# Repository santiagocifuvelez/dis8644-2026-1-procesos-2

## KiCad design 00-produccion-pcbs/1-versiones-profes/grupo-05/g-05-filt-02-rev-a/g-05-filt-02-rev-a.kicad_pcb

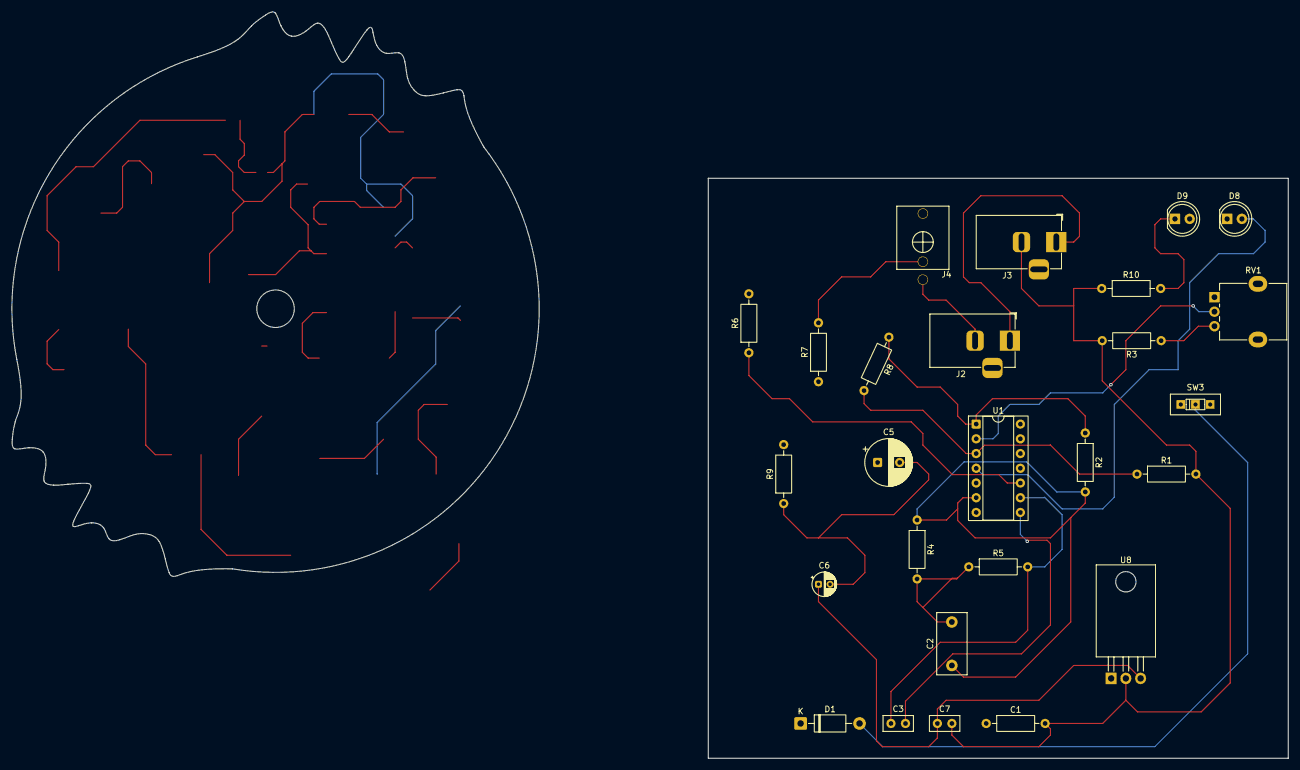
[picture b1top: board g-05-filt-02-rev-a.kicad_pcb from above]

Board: 2 copper layers, 100.0 x 100.0 mm, 26 parts (0 on the bottom side), 16 nets.

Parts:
C1: 1uf; R_Axial_DIN0207_L6.3mm_D2.5mm_P10.16mm_Horizontal
C2: 33n; C_Disc_D10.5mm_W5.0mm_P7.50mm
C3: 10n; C_Disc_D5.0mm_W2.5mm_P2.50mm
C5: 100u; CP_Radial_D8.0mm_P3.80mm
C6: 10u; CP_Radial_D4.0mm_P2.00mm
C7: 100n; C_Disc_D5.0mm_W2.5mm_P2.50mm
D1: 1N4007; D_DO-41_SOD81_P10.16mm_Horizontal
D8, D9: LED; LED_D5.0mm
J2, J3: Barrel_Jack_Switch; BarrelJack_Horizontal
J4: AudioJack2_SwitchT; PJ301M-12
R1: 22k; R_Axial_DIN0207_L6.3mm_D2.5mm_P10.16mm_Horizontal
R2, R3: 10k; R_Axial_DIN0207_L6.3mm_D2.5mm_P10.16mm_Horizontal
R4, R5, R6, R8: 100k; R_Axial_DIN0207_L6.3mm_D2.5mm_P10.16mm_Horizontal
R7: 220k; R_Axial_DIN0207_L6.3mm_D2.5mm_P10.16mm_Horizontal
R9, R10: 1k; R_Axial_DIN0207_L6.3mm_D2.5mm_P10.16mm_Horizontal
RV1: 100k; Potentiometer_Alpha_RD901F-40-00D_Single_Vertical
SW3: SW_SPDT; spdt_ssd12d00g3
U1: LM324; DIP-14_W7.62mm_Socket
U8: L7805; TO-220-3_Horizontal_TabDown

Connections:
+5V: C6.1, C7.1, D8.2 (A), U1.4 (V+), U8.3 (OUT)
+12V: C5.1, D1.1 (K), U8.1 (IN)
GND: C1.2, C5.2, C6.2, C7.2, J2.2, J3.2, J4.1, R1.2, R3.2, R6.2, R9.1, R10.1, U1.11 (V-), U8.2 (GND)
unnamed: C2.2, R4.2, R5.1, U1.7
unnamed: D1.2 (A), SW3.2 (B)
unnamed: D8.1 (K), R9.2
unnamed: C3.2, D9.2 (A), J4.3, R7.2, U1.8
unnamed: D9.1 (K), R10.2
unnamed: R2.1, R8.1, U1.1
unnamed: J2.1, J3.1, SW3.1 (A)
unnamed: R1.1, R8.2, U1.3 (+)
unnamed: C1.1, RV1.2, U1.2 (-)
unnamed: C2.1, R2.2, R4.1, U1.6 (+)
unnamed: R3.1, RV1.3, U1.5 (-)
unnamed: C3.1, R5.2, R7.1, U1.9 (+)
unnamed: R6.1, U1.10 (-)

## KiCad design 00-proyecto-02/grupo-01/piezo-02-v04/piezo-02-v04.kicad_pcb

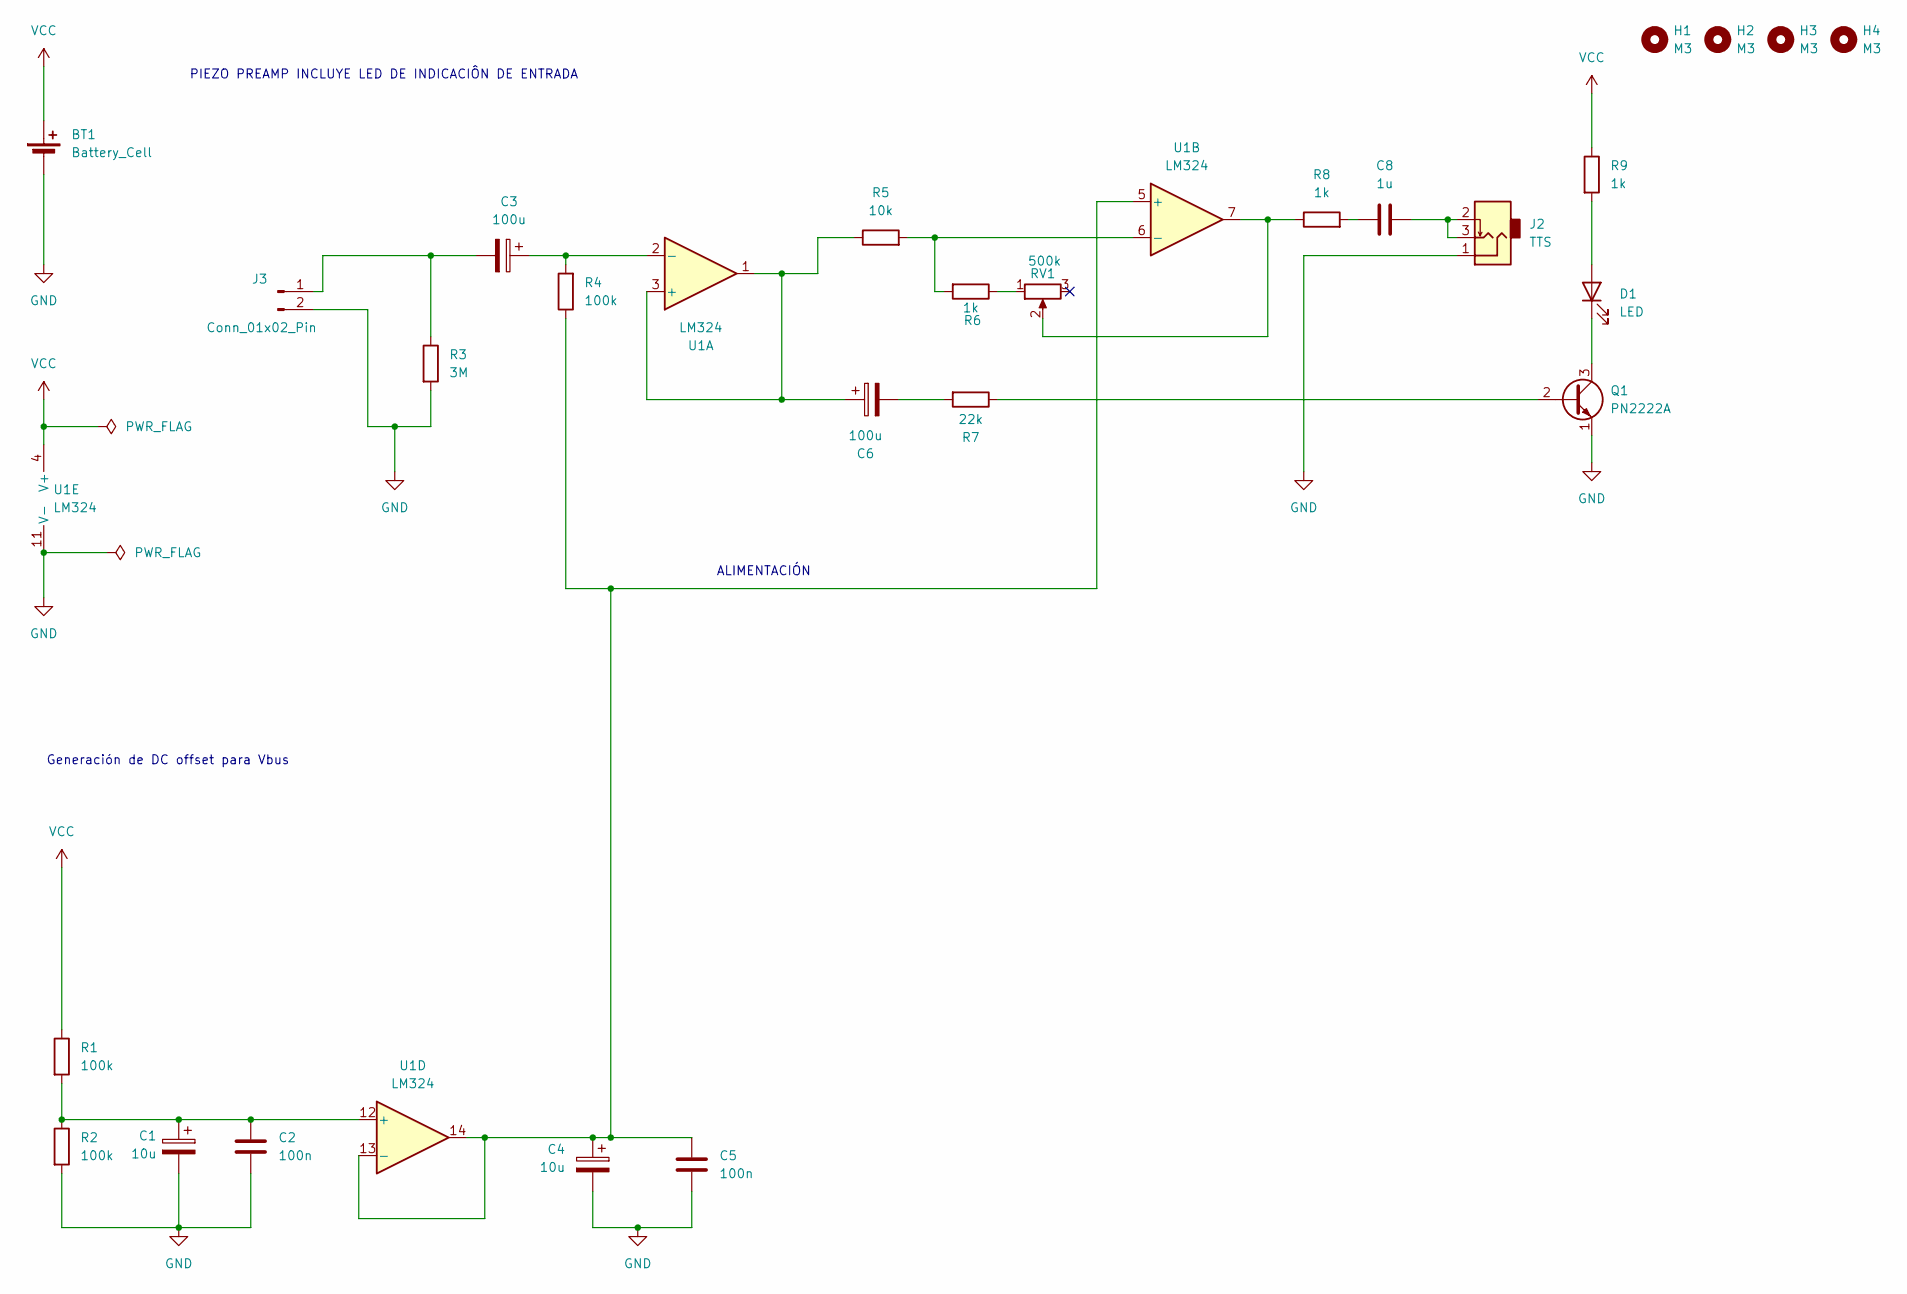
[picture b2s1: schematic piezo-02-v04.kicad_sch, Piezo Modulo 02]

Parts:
BT1: Battery_Cell; TerminalBlock_MaiXu_MX126-5.0-02P_1x02_P5.00mm
C1, C4: 10u; CP_Radial_D4.0mm_P2.00mm
C2, C5: 100n; C_Disc_D5.0mm_W2.5mm_P2.50mm
C3, C6: 100u; CP_Radial_D8.0mm_P3.80mm
C8: 1u; C_Disc_D5.0mm_W2.5mm_P5.00mm
D1: LED; LED_D5.0mm
H1, H2, H3, H4: M3; MountingHole_3.2mm_M3
J2: TTS; PJ301M-12
J3: Conn_01x02_Pin; PinSocket_1x02_P2.54mm_Vertical
Q1: PN2222A; TO-92_Inline
R1, R2, R4: 100k; R_Axial_DIN0207_L6.3mm_D2.5mm_P10.16mm_Horizontal
R3: 3M; R_Axial_DIN0207_L6.3mm_D2.5mm_P10.16mm_Horizontal
R5: 10k; R_Axial_DIN0207_L6.3mm_D2.5mm_P10.16mm_Horizontal
R6, R8, R9: 1k; R_Axial_DIN0207_L6.3mm_D2.5mm_P10.16mm_Horizontal
R7: 22k; R_Axial_DIN0207_L6.3mm_D2.5mm_P10.16mm_Horizontal
RV1: 500k; Potentiometer_Alps_RK163_Single_Horizontal
U1: LM324; DIP-14_W7.62mm_LongPads

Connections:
GND: BT1.2 (-), C1.2, C2.2, C4.2, C5.2, J2.1, J3.2, Q1.1 (E), R2.2, R3.2, U1.11 (V-)
unnamed: C6.2, R7.2
unnamed: C8.1, R8.2
unnamed: C8.2, J2.2, J2.3
unnamed: D1.2 (A), R9.2
unnamed: D1.1 (K), Q1.3 (C)
unnamed: C3.2, J3.1, R3.1
unnamed: Q1.2 (B), R7.1
unnamed: R6.1, RV1.1
unnamed: R8.1, RV1.2, U1.7
unnamed: C6.1, R5.1, U1.1, U1.3 (+)
unnamed: C3.1, R4.2, U1.2 (-)
unnamed: C4.1, C5.1, R4.1, U1.5 (+), U1.13 (-), U1.14
unnamed: R5.2, R6.2, U1.6 (-)
unnamed: C1.1, C2.1, R1.2, R2.1, U1.12 (+)
VCC: BT1.1 (+), R1.1, R9.1, U1.4 (V+)

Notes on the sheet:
PIEZO PREAMP INCLUYE LED DE INDICACIÔN DE ENTRADA
ALIMENTACIÓN
Generación de DC offset para Vbus

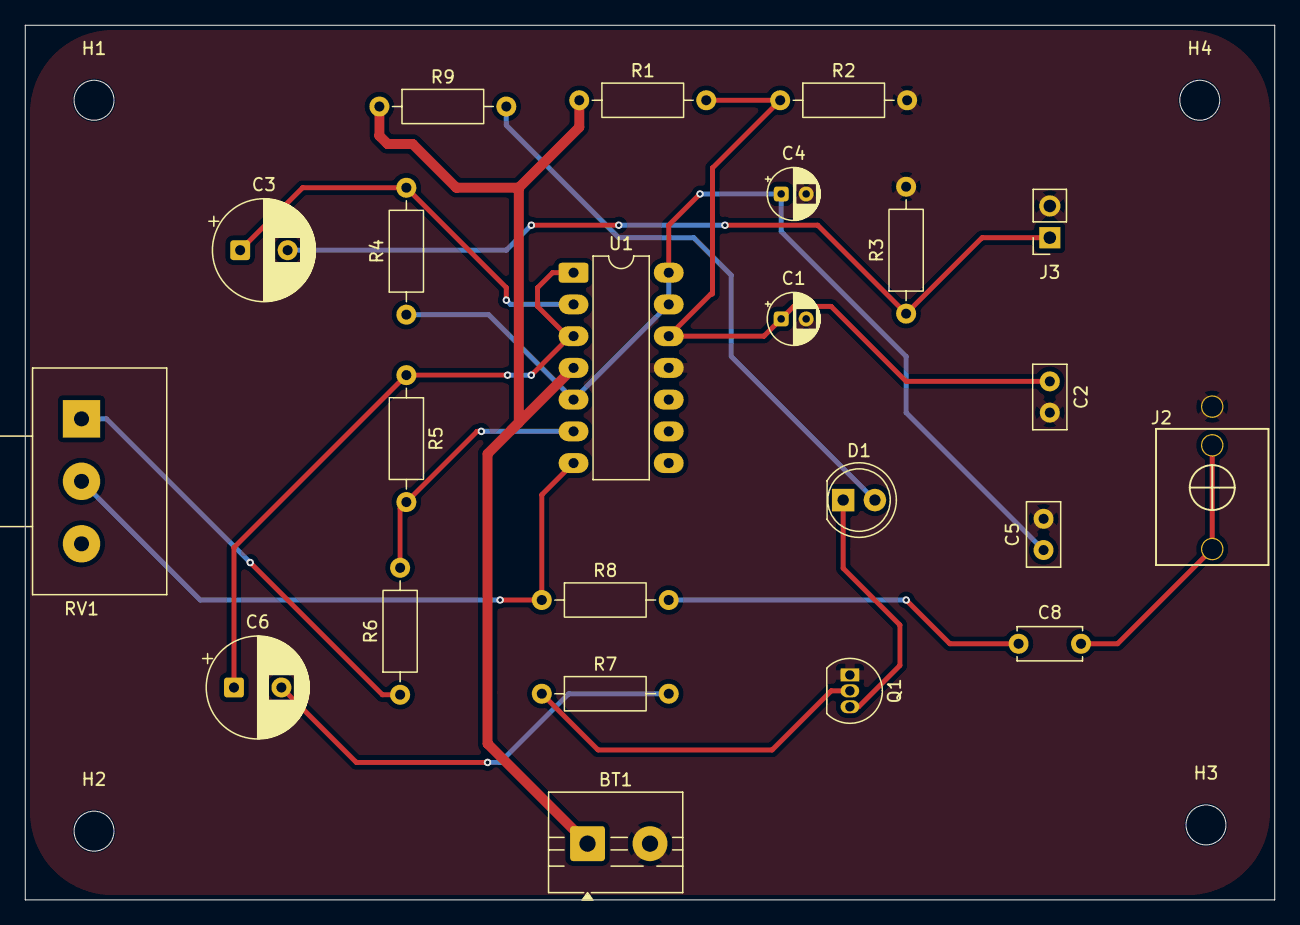
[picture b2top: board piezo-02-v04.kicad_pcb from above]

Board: 2 copper layers, 100.0 x 70.0 mm, 27 parts (0 on the bottom side), 16 nets.

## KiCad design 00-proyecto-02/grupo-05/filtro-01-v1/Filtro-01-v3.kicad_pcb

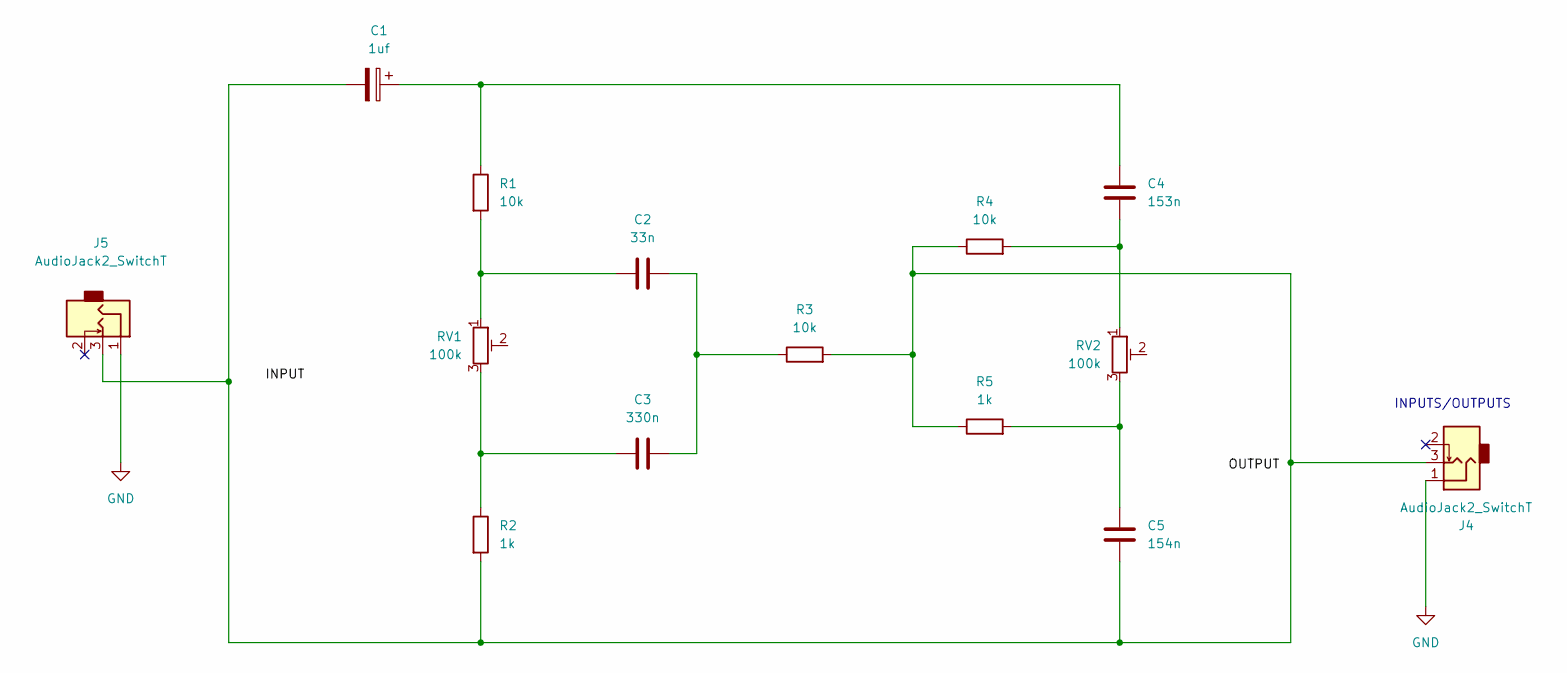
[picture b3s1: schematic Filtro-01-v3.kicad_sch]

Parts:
C1: 1uf; CP_Radial_D5.0mm_P2.00mm
C2: 33n; C_Disc_D10.5mm_W5.0mm_P7.50mm
C3: 330n; C_Disc_D7.5mm_W5.0mm_P10.00mm
C4: 153n; C_Disc_D6.0mm_W2.5mm_P5.00mm
C5: 154n; C_Disc_D7.5mm_W4.4mm_P5.00mm
J4, J5: AudioJack2_SwitchT; PJ301M-12
R1, R3, R4: 10k; R_Axial_DIN0207_L6.3mm_D2.5mm_P2.54mm_Vertical
R2, R5: 1k; R_Axial_DIN0207_L6.3mm_D2.5mm_P2.54mm_Vertical
RV1, RV2: 100k; Potentiometer_Bourns_PTV09A-1_Single_Vertical

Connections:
GND: J4.1, J5.1
unnamed: C1.1, C4.1, R1.1
unnamed: C1.2, C5.2, J4.3, J5.3, R2.2, R3.2, R4.1, R5.1
unnamed: C2.1, R1.2, RV1.1
unnamed: C2.2, C3.2, R3.1
unnamed: C3.1, R2.1, RV1.3
unnamed: C4.2, R4.2, RV2.1
unnamed: C5.1, R5.2, RV2.3

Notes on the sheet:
INPUTS/OUTPUTS

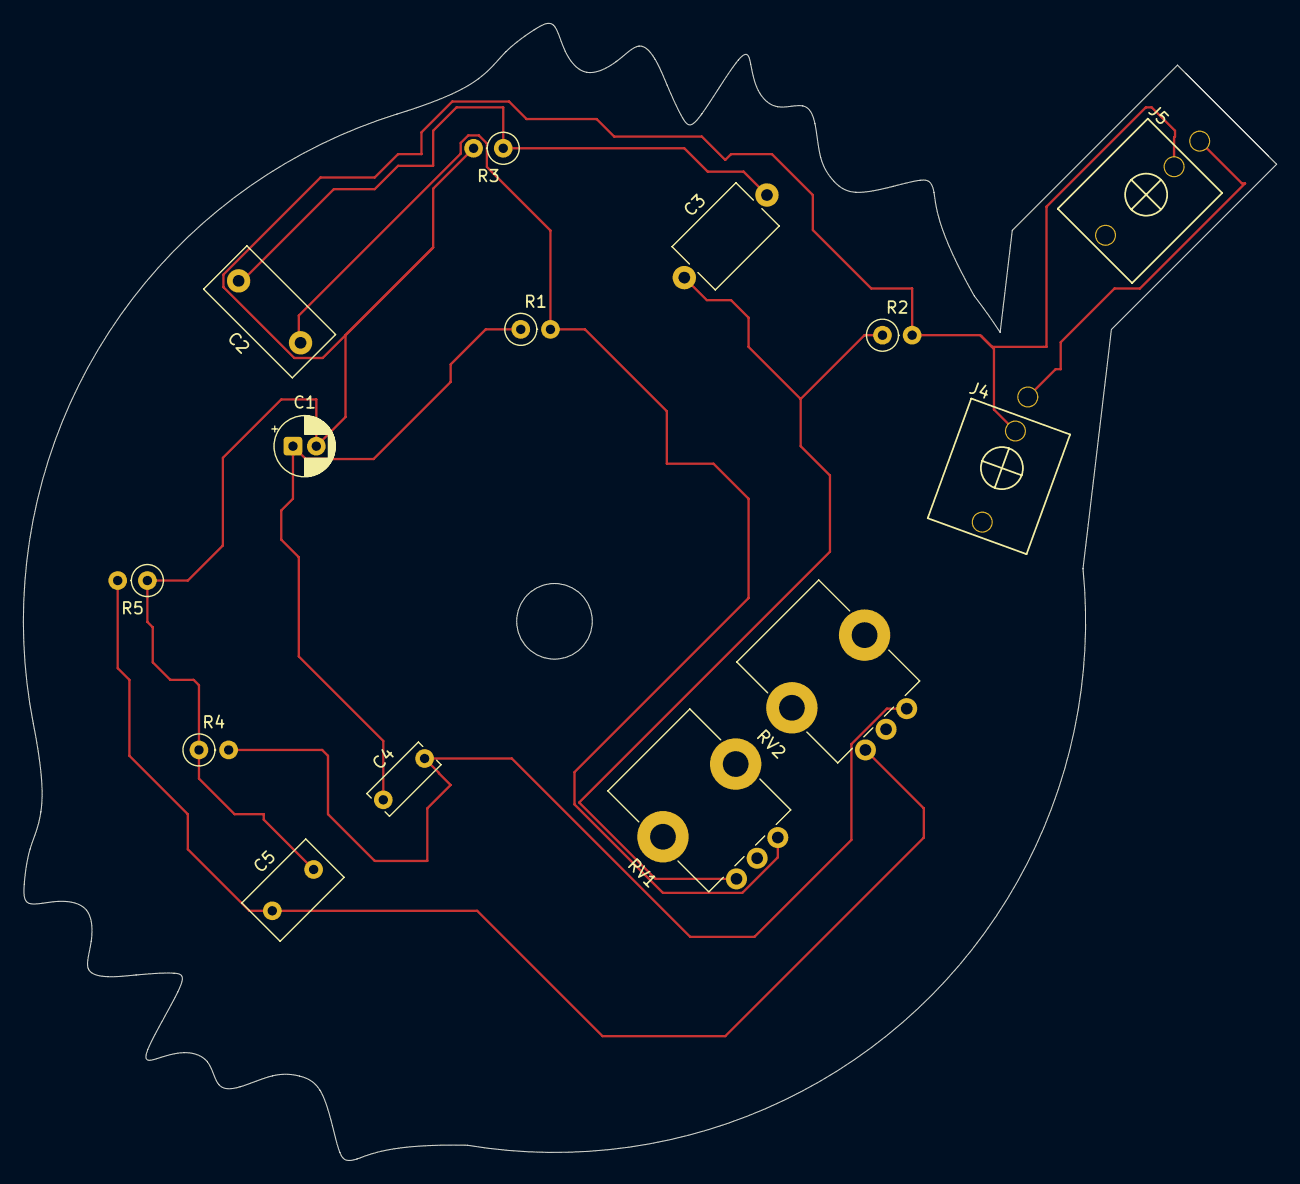
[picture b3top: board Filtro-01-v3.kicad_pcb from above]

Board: 2 copper layers, 107.3 x 97.3 mm, 14 parts (0 on the bottom side), 8 nets.
